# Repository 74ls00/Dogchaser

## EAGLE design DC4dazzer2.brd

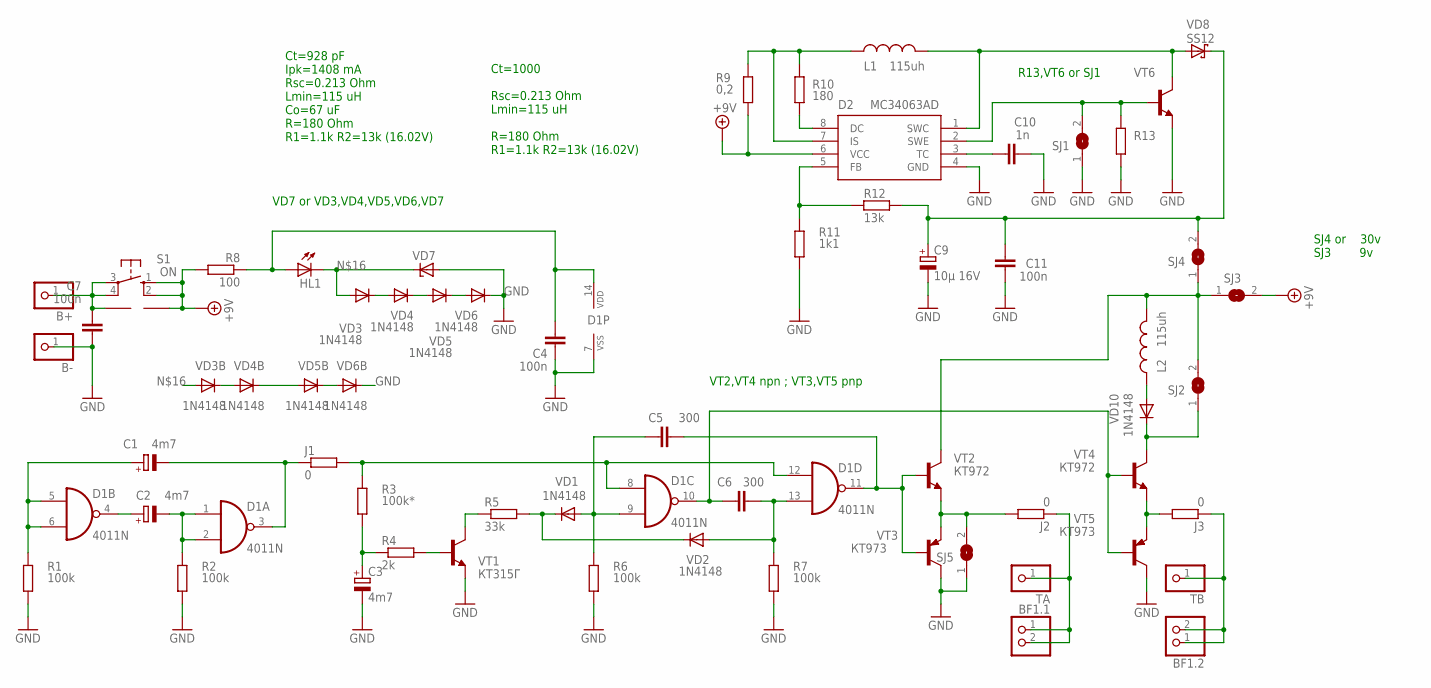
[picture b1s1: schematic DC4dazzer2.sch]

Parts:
B+: PINHD-1X1; 1X01
B-: PINHD-1X1; 1X01
BF1.1, BF1.2: PINHD-1X2; 1X02
C1: 4m7; E3,5-8
C2, C3: 4m7; E2,5-7
C4, C11: 100n; C0805
C5, C6: 300; CAP-PTH-LARGE
C7: 100n; C025-024X044
C9: 10µ 16V; RCL_E3,5-8
C10: 1n; C025-025X050
D1: 4011N; DIL14
D2: MC34063AD; SOIC8
HL1: LED5MM
J1, J2, J3: 0; R1206W
L1: 115uh; 0207/10
L2: 115uh; 0204/5
R1, R2: 100k; R0805
R3: 100k*; 0204/7
R4: 2k; R0805
R5: 33k; R1206W
R6: 100k; R1206W
R7: 100k; M0805
R8: 100; 0204/5
R9: 0,2; 0204/7
R10: 180; 0204/7
R11: 1k1; M0805
R12: 13k; M0805
R13: R-EU_0204/7; 0204/7
S1: ON; B3F-10XX
SJ1, SJ2, SJ3, SJ4, SJ5: SJ
TA: PINHD-1X1; 1X01
TB: PINHD-1X1; 1X01
U$2: PROGRAMMER_5.08; PROGRAMMER_KEY
VD1, VD2, VD3B, VD4B, VD5B, VD6B, VD10: 1N4148; SOD80C
VD3, VD4, VD5, VD6: 1N4148; DO35-7
VD7: ZENER-DIODEZD-7.5; ZDIO-7.5
VD8: SS12; SMB
VT1: КТ315Г; TO92-ECB
VT2, VT4: КТ972; TO92-ECB
VT3, VT5: КТ973; TO92-BCE
VT6: BC167-NPN-TO92-ECB; TO92-ECB

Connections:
+9V: D2.6 (VCC), R8.2, R9.1, S1.1 (S), S1.2 (S1), SJ3.2, U$2.P$2
B+: B+.1, C7.1, S1.3, S1.4 (P1), U$2.P$1
GND: B-.1, C3.-, C4.2, C7.2, C9.-, C10.2, C11.1, D1.7 (VSS), D2.4 (GND), R1.1, R2.1, R6.1, R7.1, R11.1, R13.1, SJ1.1, SJ5.1, VD6.C, VD6B.C, VD7.A, VT1.E, VT3.C, VT5.C, VT6.E
unnamed: C1.+, D1.5 (I0), D1.6 (I1), R1.2
unnamed: C2.+, D1.4 (O)
unnamed: C2.-, D1.1 (I0), D1.2 (I1), R2.2
unnamed: D1.8 (I0), D1.12 (I0), J1.2, R3.2
unnamed: C3.+, R3.1, R4.1
unnamed: R4.2, VT1.B
unnamed: R5.1, VT1.C
unnamed: R5.2, VD1.C, VD2.C
unnamed: C5.1, D1.9 (I1), R6.2, VD1.A
unnamed: C6.1, D1.10 (O), VT4.B, VT5.B
unnamed: C6.2, D1.13 (I1), R7.2, VD2.A
unnamed: J2.2, SJ5.2, VT2.E, VT3.E
unnamed: J3.2, VT4.E, VT5.E
unnamed: C5.2, D1.11 (O), VT2.B, VT3.B
unnamed: C1.-, D1.3 (O), J1.1
unnamed: HL1.K (C), VD3.A, VD3B.A, VD7.C
unnamed: D2.8 (DC), R10.1
unnamed: BF1.2.1, BF1.2.2, J3.1, TB.1
unnamed: D2.7 (IS), L1.1, R9.2, R10.2
unnamed: VD3.C, VD3B.C, VD4.A, VD4B.A
unnamed: VD4.C, VD4B.C, VD5.A, VD5B.A
unnamed: VD5.C, VD5B.C, VD6.A, VD6B.A
unnamed: BF1.1.1, BF1.1.2, J2.1, TA.1
unnamed: D2.5 (FB), R11.2, R12.1
unnamed: D2.2 (SWE), R13.2, SJ1.2, VT6.B
unnamed: C10.1, D2.3 (TC)
unnamed: D2.1 (SWC), L1.2, VD8.A, VT6.C
unnamed: C9.+, C11.2, R12.2, SJ4.2, VD8.C
unnamed: L2.1, VD10.A
unnamed: SJ2.1, VD10.C, VT4.C
unnamed: L2.2, SJ2.2, SJ3.1, SJ4.1, VT2.C
~+5V: C4.1, D1.14 (VDD), HL1.A, R8.1

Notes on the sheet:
Ct=928 pF Ipk=1408 mA Rsc=0.213 Ohm Lmin=115 uH Co=67 uF R=180 Ohm R1=1.1k R2=13k (16.02V)
Ct=1000 Rsc=0.213 Ohm Lmin=115 uH R=180 Ohm R1=1.1k R2=13k (16.02V)
VD7 or VD3,VD4,VD5,VD6,VD7
R13,VT6 or SJ1
VT2,VT4 npn ; VT3,VT5 pnp
SJ4 or 30v SJ3 9v

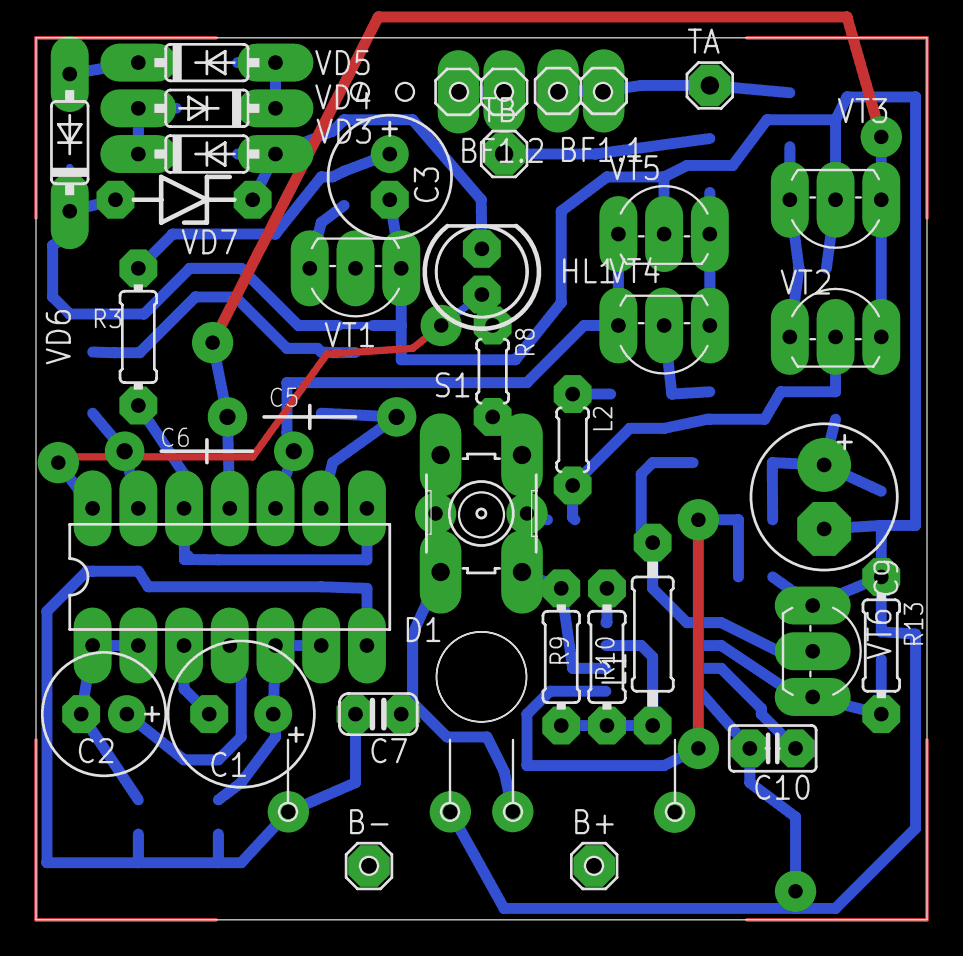
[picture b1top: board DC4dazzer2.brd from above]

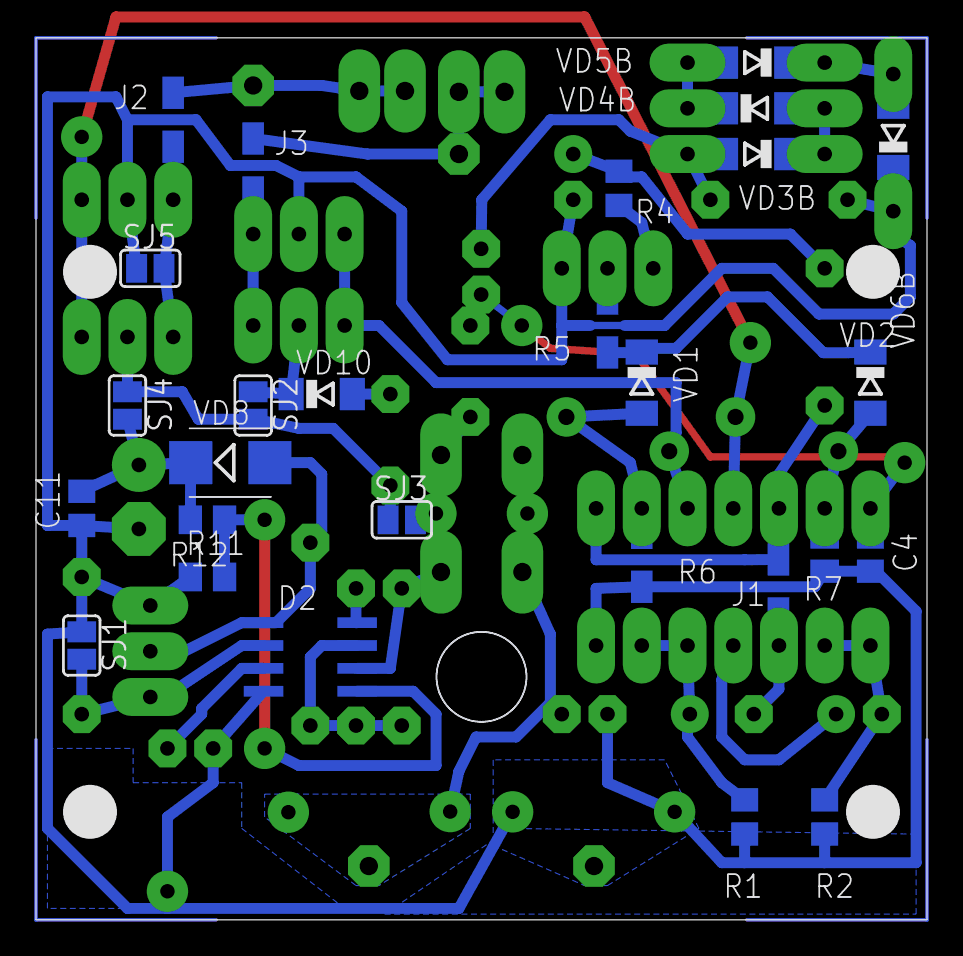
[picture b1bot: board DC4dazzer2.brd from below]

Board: 2 copper layers, 49.4 x 48.9 mm, 64 parts (27 on the bottom side), 35 nets.

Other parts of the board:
U$1: DAZZER2PL

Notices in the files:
parts and their libraries:
SparkFun-Capacitors: Licensing: Creative Commons ShareAlike 4.0 International - https://creativecommons.org/licenses/by-sa/4.0
